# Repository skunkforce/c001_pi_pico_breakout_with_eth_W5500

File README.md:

# edgy_board number c001
This design is part of the [edgy board project](https://github.com/skunkforce/edgy_boards).

This design is a composition of edgies.
```mermaid
graph LR
    b018(b018 RP2040)-- SPI -->b078(b078 Ethernet MAC+PHY)
    b018--> b096(b096 MAC ID)

```
# getting started
This repository uses submodules. After cloning use the command 

```$ git submodule update --init --recursive```

to pull the submodules before opening the project with kicad. 

# Tests
Tests can be found in [TESTS.md](TESTS.md)

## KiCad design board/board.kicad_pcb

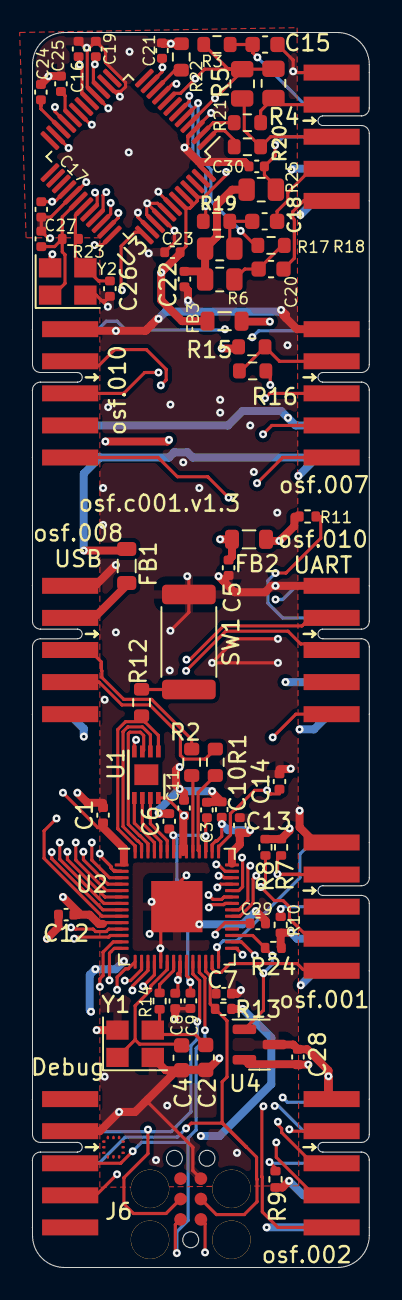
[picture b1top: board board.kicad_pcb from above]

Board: 4 copper layers, 21.0 x 77.0 mm, 75 parts (1 on the bottom side), 76 nets.

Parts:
C1, C3, C5, C6, C8, C10, C11, C12, C16, C17, C19, C21, C23, C28, C29, C30: 100nF; C_0402_1005Metric
C2, C4: 12pF; C_0603_1608Metric
C7: 1uF; C_0402_1005Metric
C9, C13, C14: 2.2uF; C_0402_1005Metric
C15: 22nF; C_0603_1608Metric
C18, C20: 6.8nF; C_0603_1608Metric
C22, C24: 10nF; C_0402_1005Metric
C25: 4.7uF; C_0402_1005Metric
C26, C27: 18pF; C_0402_1005Metric
FB1: Ferrite_Bead_Small; L_0805_2012Metric
FB2, FB3: FerriteBead_Small; L_0805_2012Metric
J1: UART; on_edge_2x05_device
J2: 008_USB; on_edge_2x05_device
J3: DebugEdge_02x05; debug_edge_2x05_device
J4: 019_100BASE-T_with_CT; on_edge_2x05_host
J5: ADC_2x3; on_edge_2x05_host
J6: SWD_6_Pol_Needle; SWD6pol
J7: SPI_2x3; on_edge_2x05_host
J8: I2C_2x2; on_edge_2x05_host
J9: UART_2x2; on_edge_2x05_host
LOGO1: Logo_Open_Hardware_Small; OSHW-Symbol_6.7x6mm_SilkScreen
R1, R2: 27R; R_0603_1608Metric
R3: 10R; R_0603_1608Metric
R4, R5, R6, R17: 49.9R; R_0805_2012Metric
R7, R8, R24: 2k; R_0402_1005Metric
R9, R10, R11, R13: 10k; R_0402_1005Metric
R12: 1k; R_0603_1608Metric
R14: 1k; R_0402_1005Metric
R15: 200R; R_0603_1608Metric
R16: 1R; R_0603_1608Metric
R18, R19, R20, R21: 3.3R; R_0603_1608Metric
R22: 12.4k; R_0603_1608Metric
R23: 1M; R_0402_1005Metric
R25: d.n.p; R_0805_2012Metric
SW1: PTS636 SK25J SMTR LFS; R_2512_6332Metric
U1: W25Q16JVUXIQ; DFN-8-1EP_3x2mm_P0.5mm_EP1.3x1.5mm
U2: RP2040; QFN-56-1EP_7x7mm_P0.4mm_EP3.2x3.2mm
U3: W5500; LQFP-48_7x7mm_P0.5mm
U4: 11AA02E48; SOT-23
Y1: 12MhZ; Crystal_SMD_Abracon_ABM8G-4Pin_3.2x2.5mm
Y2: 25MhZ; Crystal_SMD_Abracon_ABM8G-4Pin_3.2x2.5mm

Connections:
+3.3V: C28.1, FB2.1, FB3.2, J1.9 (3.3V), J4.9 (3.3V), J5.9 (3.3V), J7.9 (3.3V), J8.9 (3.3V), J9.9 (3.3V), R7.1, R8.1, R9.1, R10.1, R11.1, R24.1, U4.2 (VCC)
+5V: FB1.1, J1.10 (5V), J2.10 (5V), J4.10 (5V), J5.10 (5V), J7.10 (5V), J8.10 (5V), J9.10 (5V)
/ADC0: J5.3 (ADC0), U2.38 (GPIO26_ADC0)
/ADC1: J5.4 (ADC1), U2.39 (GPIO27_ADC1)
/ADC2: J5.5 (ADC2), U2.40 (GPIO28_ADC2)
/ADC3: J5.6 (ADC3), U2.41 (GPIO29_ADC3)
/ADC_VREF: J5.2 (VREF), R15.2, R16.1
/DM: R1.2, U2.46 (USB_DM)
/DP: R2.2, U2.47 (USB_DP)
/GPIO14: J7.5 (INT), U2.17 (GPIO14)
/GPIO15: J7.7 (status), U2.18 (GPIO15)
/GPIO16: J8.5 (INT), U2.27 (GPIO16)
/GPIO17: J8.6 (CS/EN), U2.28 (GPIO17)
/GPIO22: J9.6 (CS/EN), U2.34 (GPIO22)
/GPIO23: J9.5 (INT), U2.35 (GPIO23)
/GPIO24: J1.5 (INT), U2.36 (GPIO24)
/GPIO25: J1.6 (CS/EN), U2.37 (GPIO25)
/I2C1_SCL: J8.4 (SCL), R8.2, U2.30 (GPIO19)
/I2C1_SDA: J8.2 (SDA), R7.2, U2.29 (GPIO18)
/SPI1_RX: J7.3 (MISO), U2.15 (GPIO12)
/SPI1_SCK: J7.4 (SCLK), U2.13 (GPIO10)
/SPI1_TX: J7.2 (MOSI), U2.14 (GPIO11)
/UART0_RX: J1.2 (TX), U2.3 (GPIO1)
/UART0_TX: J1.3 (RX), U2.2 (GPIO0)
/UART1_RX: J9.3 (RX), U2.12 (GPIO9)
/UART1_TX: J9.2 (TX), U2.11 (GPIO8)
/controller/1V2O: C24.2, U3.22 (1V2O)
/controller/CT1: C15.1, J4.7 (CT1), R3.1
/controller/CT2: C30.1, J4.8 (CT2), R25.1
/controller/RXN: C20.1, J4.5 (TD2-)
/controller/RXP: C18.1, J4.4 (TD2+)
/controller/TXN: J4.3 (TD1-), R5.1, R20.1
/controller/TXP: J4.2 (TD1+), R4.1, R21.1
/controller/VDD: C16.1, C17.1, C19.1, C21.1, C23.1, FB3.1, R3.2, R4.2, R5.2, U3.4 (AVDD), U3.8 (AVDD), U3.11 (AVDD), U3.15 (AVDD), U3.17 (AVDD), U3.21 (AVDD), U3.28 (VDD), U3.43 (PMODE2), U3.44 (PMODE1), U3.45 (PMODE0)
/controller/XCAP: C25.1, U3.20 (TOCAP)
/controller/XI: C27.1, R23.1, U3.30 (XI), Y2.1
/controller/XO: C26.1, R23.2, U3.31 (XO), Y2.3
/controller/XRES: R22.1, U3.10 (EXRES)
/mac/IO: R24.2, U2.31 (GPIO20), U4.1 (SCIO)
/rp2040/GPIO6: U2.8 (GPIO6), U3.36 (INT)
/rp2040/GPIO7: U2.9 (GPIO7), U3.37 (RESET)
/rp2040/QPI_SS: R12.2, U1.1 (~CS), U2.56 (QSPI_SS)
/rp2040/QSPI_CLK: U1.6 (CLK), U2.52 (QSPI_SCLK)
/rp2040/RUN: C7.1, J3.4 (~RESET), J6.3 (nRes), R13.2, U2.26 (RUN)
/rp2040/SPI0_RX: U2.6 (GPIO4), U3.34 (MISO)
/rp2040/SPI0_SCK: U2.4 (GPIO2), U3.33 (SCLK)
/rp2040/SPI0_TX: U2.5 (GPIO3), U3.35 (MOSI)
/rp2040/SWCLK: J3.3 (SWDCLK/TCLK), J6.4 (SWCLK), U2.24 (SWCLK)
/rp2040/SWD: J3.2 (SWDIO/TMS), J6.2 (SWDIO), U2.25 (SWD)
/rp2040/~SPI0_CS: U2.7 (GPIO5), U3.32 (CS)
/uC3.3V: C1.1, C5.1, C8.1, C10.1, C11.1, C12.1, C13.1, C29.1, FB2.2, J3.5 (Vref), J6.1 (VTref), R13.1, R15.1, U1.8 (VCC), U2.1 (IOVDD), U2.10 (IOVDD), U2.22 (IOVDD), U2.33 (IOVDD), U2.42 (IOVDD), U2.44 (VREG_IN), U2.48 (USB_VDD), U2.49 (IOVDD)
/~SPI1_CS: J7.6 (CS), U2.16 (GPIO13)
GND: C1.2, C2.2, C3.2, C4.2, C5.2, C6.2, C7.2, C8.2, C9.2, C10.2, C11.2, C12.2, C13.2, C14.2, C15.2, C16.2, C17.2, C19.2, C21.2, C22.2, C23.2, C24.1, C25.2, C26.2, C27.2, C28.2, C29.2, C30.2, J1.1 (GND), J2.1 (GND), J3.1 (GND), J4.1 (GND), J4.6 (GND), J5.1 (GND), J6.5 (GND), J7.1 (GND), J8.1 (GND), J9.1 (GND), R22.2, SW1.1, U1.4 (GND), U2.19 (TESTEN), U2.57 (GND), U3.3 (AGND), U3.9 (AGND), U3.14 (AGND), U3.16 (AGND), U3.19 (AGND), U3.23 (RSVD), U3.29 (GND), U3.38 (RSVD), U3.39 (RSVD), U3.40 (RSVD), U3.41 (RSVD), U3.42 (RSVD), U3.48 (AGND), U4.3 (GND), Y1.2, Y1.4, Y2.2, Y2.4
unnamed: C2.1, R14.1, Y1.3
unnamed: C18.2, R17.2, R19.1
unnamed: C20.2, R6.2, R18.1
unnamed: C22.1, R6.1, R17.1, R25.2
unnamed: J2.4 (DM), R1.1
unnamed: J2.3 (DP), R2.1
unnamed: FB1.2, J2.2 (VBUS)
unnamed: J7.8 (~RESET), R9.2
unnamed: J8.8 (~RESET), R10.2
unnamed: J9.7 (~RESET), R11.2
unnamed: R12.1, SW1.2
unnamed: U1.5 (DI(IO0)), U2.53 (QSPI_SD0)
unnamed: U1.2 (DO(IO1)), U2.55 (QSPI_SD1)
unnamed: U1.3 (IO2), U2.54 (QSPI_SD2)
unnamed: U1.7 (IO3), U2.51 (QSPI_SD3)
unnamed: C14.1, R16.2, U2.43 (ADC_AVDD)
unnamed: C3.1, C6.1, C9.1, U2.23 (DVDD), U2.45 (VREG_VOUT), U2.50 (DVDD)
unnamed: C4.1, U2.20 (XIN), Y1.1
unnamed: R14.2, U2.21 (XOUT)
unnamed: R18.2, U3.5 (RXIN)
unnamed: R19.2, U3.6 (RXIP)
unnamed: R20.2, U3.1 (TXON)
unnamed: R21.2, U3.2 (TXOP)

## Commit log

2023-02-28 added submodules
2023-02-28 updated schemetic and layout
2023-02-28 updated board picture
2023-02-28 added needle addapter
2023-03-01 added power planes
2023-03-01 improved power integrity
2023-03-01 improved board emc
2023-03-03 improved EMC
2023-03-04 updated put_on_edge connectors
2023-05-09 updated to use v1.1 of b078 to work with shorted center tap magjacks
2023-11-28 added boot select button and standard (small) flash
2023-12-29 fixed I2C pinning defect
2024-01-05 moved all components to top layer
2024-02-24 added lcsc part numbers
